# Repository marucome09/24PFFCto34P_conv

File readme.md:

# 24PFFCto34P_conv

This is 24PFFC FDD I/F(Matsushita/Panasonic EME-213xx) convert to FDD for PC(or a gotek with FlashFloppy)compatible.

(24PFFC I/F used to Yamaha QY300/SY85/MDF2/W5/W7, etc)

松下 EME-213xx FDDの24PinFFCの信号線を、PC用34Pに変換するボードです。

(Yamaha QY300/SY85/MDF2/W5/W7等多くに使用されています)

注意：この機器の取り付けによって起きたいかなるトラブルに対しても、当方は（スイッチサイエンス様で販売いただいている製品版についての製品不良時の製品交換以外）一切の責任を負いかねます。取り付けに際しては細心の注意を払い、慎重に取り付けてください。

詳細はWikiを参照ください。

[to Wiki Page](../../wiki)

# Features　おすすめポイント
- Designed to be attached directly to FDD(or emulator).

- 設計上直接FDDに取り付けられるので、場所を取らず、両面テープを用意する必要がありません（ただしFDDによっては34ピンコネクタの上部を絶縁テープなどで絶縁する必要があります）。

- このボードは、HxC for Gotek, Flashfloppy(for Gotek hardware)、PC用FDDに幅広く対応します。

注意：スイッチサイエンス様より発売する製品版につきましては、写真にあります電源部のコネクタはオミットされておりますのでご了承ください。

コストというよりは、FDDコネクタより後ろのマージンを稼ぐ狙いがあります（コネクタをつけると数ミリ余計にスペースを取るため）。ケーブルはもともとついているケーブルを利用します。

# Requirement 制作に必要な部品

4k7 pull-up resistor / 4.7k 抵抗（1/4W）

34P(17x2) pin-socket / 34ピン　ピンソケット（FDDコネクタ直差し用）

Molex 52045-2445 24PFFC /　24ピン FFCコネクタ（24P I/Fケーブル用）

1x3 pin-header / 1x3 ピンヘッダ（ジャンパ用）

Novo Shunt Connector / ジャンパーピン（ジャンパ）

2P EI pin-header / 2P EI ピンヘッダ（ボードからの電源取り出し用）※

2P EI connector housing & contact / 2P EIコネクタハウジング＆コンタクト（ボードからの電源取り出し用）※

4P EI connector housing & contact / 4P EIコネクタハウジング＆コンタクト（FDD電源用）

Power Cable(~20cm)

※他のコネクタでも代用可能、また基板直付けでもOK

# Making

コネクタ類を写真のようにはんだ付けします。

まず、基板表面に抵抗を取り付け、24P FFCコネクタを、切り欠きが左端になるように取り付け、はんだ付けします。

電源の２P端子(左上）は、コネクタ側（内側）が＋極になっています。その下の端子には3Pピンヘッダを付けます。、

なお、FDD(もしくはエミュレーター）側の電源コネクタはこのように制作します。

# Usage

このような感じでFDD（写真はGotek FDDエミュレーターです）に取り付けます。

※写真はテスト品のため電源部にコネクタがついています。また外観や回路も一部違います。

注意：FDDにコネクタを取り付けるときは、FDDがボックスタイプになっている場合上下左右の開きが大きいため、上下左右に1，2段ずれて入ってしまう可能性があります。

必ず慎重に、ずれがないかを確認しながら取り付けてください。

また、必ず写真の向きで取り付けてください。上下逆にした場合、本体やFDD（FDDエミュレーターなど）を損傷する恐れがあります。

本体からの接続は、もともとSY85についているFFCケーブルをそのまま流用します。金属部分（接点）を必ず上にして差し込みます。

FFCの構造上1番ピンを示す切り欠きの位置が逆になりますが、これで間違いはありません。

なお、その他の機器固有の接続に関する注意点、設定についても必ずお読みください。wikiに記載しておきます。

[to Wiki Page](../../wiki)

# Note

・信号線はDS1固定のため、DS0で動作するFDDの場合はDS1に設定を変更する必要があります。

・FDD取り付け部の後ろおよび高さに十分マージンがない場合、アダプタが取り付けられない場合があります。（物理的要件）

・一部FDDには取り付け不可能です（ミツミ D353M3Dなど、電源コネクタが信号コネクタの真上にある場合など）（物理的要件）

☆なお、FDDエミュレーターはGotek純正では動作確認を行っておりません。必ずファームウェアを書き換えてご使用ください。

☆HxC SD Floppy Emulator（Rev.F）を使用の場合、機器長の関係で取り付けが困難になる可能性があります。

- コネクタの直上までFDDのフレームや、金属カバーが伸びてきているタイプの場合、変換コネクタの金属部分が当たってショートする恐れがあります。（写真のような場合）

この場合は、当たる面、つまり26ピンコネクタの裏側に（下の写真の赤で囲った部分を中心に全体的に）絶縁テープなどを使って絶縁してください。

このほかにも、フレームや筺体などの金属部分に当たりそうな場所があれば絶縁しておくことをお勧めします。

# License

This Product is CC BY-NC-SA 4.0

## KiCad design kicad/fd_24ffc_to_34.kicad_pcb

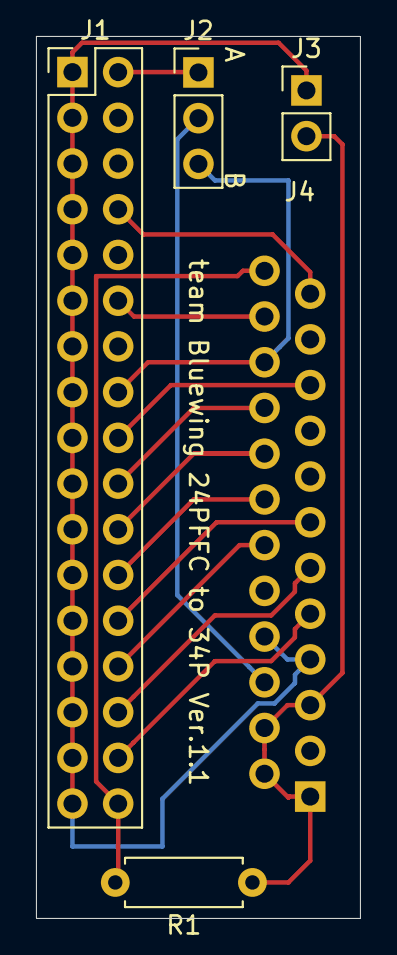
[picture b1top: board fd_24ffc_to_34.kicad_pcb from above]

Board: 2 copper layers, 18.0 x 49.0 mm, 5 parts (0 on the bottom side), 16 nets.

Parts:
J1: Conn_02x17_Odd_Even; PinHeader_2x17_P2.54mm_Vertical
J2: Conn_01x03; PinHeader_1x03_P2.54mm_Vertical
J3: Conn_01x02; PinHeader_1x02_P2.54mm_Vertical
J4: FD_FFC_24p; Molex_52045-2445_24p
R1: R; R_Axial_DIN0207_L6.3mm_D2.5mm_P7.62mm_Horizontal

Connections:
+5V: J3.2, J4.1, J4.2, J4.4, J4.5, R1.1
GND: J1.1, J1.3, J1.5, J1.7, J1.9, J1.11, J1.13, J1.15, J1.17, J1.19, J1.21, J1.23, J1.25, J1.27, J1.29, J1.31, J1.33, J3.1, J4.7, J4.8
unnamed: J1.2, J2.1
unnamed: J1.8, J4.23
unnamed: J1.12, J4.22
unnamed: J1.16, J2.3, J4.20
unnamed: J1.18, J4.19
unnamed: J1.20, J4.18
unnamed: J1.22, J4.16
unnamed: J1.24, J4.14
unnamed: J1.26, J4.13
unnamed: J1.28, J4.12
unnamed: J1.30, J4.11
unnamed: J1.32, J4.9
unnamed: J1.34, J4.24, R1.2
unnamed: J2.2, J4.6

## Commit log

2025-06-06 Delete kicad/fd_24ffc_to_34.kicad_pcb
    protect
